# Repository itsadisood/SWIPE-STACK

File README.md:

# SWIPE-STACK

**SWIPE-STACK** is a modern re-implementation of the classic puzzle game *Tetris*, featuring a wireless glove controller and a dynamic LED-matrix-based main hub.

This project combines embedded systems design, wireless communication, real-time graphics processing, and custom hardware to create an innovative and portable gaming experience.

---

## Project Overview

The system consists of two main components:

### Glove Module
- **Input Device**: A wearable glove capturing hand movements and gestures.
- **Key Components**:
  - **IMU Sensor**: Collects motion and orientation data.
  - **STM32 Microcontroller**: Processes IMU data and converts it into game control inputs.
  - **HM19 Bluetooth Module**: Communicates inputs wirelessly to the hub via UART.
  - **LiPo Battery**: Powers the glove, with battery management provided by an off-the-shelf controller.

### Main Hub
- **Game Console**: Executes game logic, receives user input, and manages displays.
- **Key Components**:
  - **STM32 Microcontroller**: Runs the game engine and display drivers.
  - **HM19 Bluetooth Module**: Receives input data from the glove.
  - **64x32 LED Matrix Display**: Displays the active game screen, driven by a custom parallel interface using DMA and timers.
  - **OLED 16x2 Text Display**: Shows the current score and level via SPI.
  - **TI Buck Converter**: Provides regulated power for the system.

Each STM32 project (`Hub/` and `Glove/`) follows the typical CubeIDE structure, including source files (`Core/`), drivers (`Drivers/`), project configuration (`.ioc`), and build settings.

---

## Repository Structure

- **Hub/** – Firmware for the main hub (STM32 project using STM32Workbench)
- **Glove/** – Firmware for the glove controller (STM32 project using STM32Workbench)
- **Electrical/** – Hardware design files (schematics, PCB layouts)
- **Mechanical/** – Mechanical design files (CAD models for glove and hub enclosures)
- **README.md** – Project overview and documentation (this file)

---
## Features

- **Wireless Glove Controller**: Real-time gesture input using an IMU and STM32 MCU.
- **Bluetooth Communication**: Low-latency UART-based HM19 Bluetooth link.
- **Custom LED Matrix Driver**: High-speed, multiplexed driving of a 64x32 RGB LED matrix using DMA and timers.
- **Embedded Game Engine**: Fully on-board Tetris-like game running on STM32 microcontroller.
- **Text-Based Display**: OLED screen displaying real-time score and level information.
- **Portable and Modular Design**: Custom PCBs, enclosures, and battery-powered operation.

---

## Demo

Check out a live demo of SWIPE-STACK here:  

👉 [Watch the demo on YouTube](https://www.youtube.com/watch?v=645_PaOeo9Y&t=164s)

---

## Contributors

- Aditya Sood
- Alex Chitsazzadeh
- Vishnu Lagudu
- Justin Cambridge

---

## Notes

- This project is not intended for direct plug-and-play usage.
- Hardware assembly, flashing, and Bluetooth setup are required to build a fully functioning system.
- Schematics and mechanical models are provided for reference and reproduction.
- All firmware was developed using [STM32SystemWorkbench](https://www.st.com/en/development-tools/stm32cubeide.html).

---

## Acknowledgments

- STM32Cube HAL Drivers
- Public domain versions of the classic Tetris game logic
- Open-source hardware design inspirations for LED matrix driving techniques

---

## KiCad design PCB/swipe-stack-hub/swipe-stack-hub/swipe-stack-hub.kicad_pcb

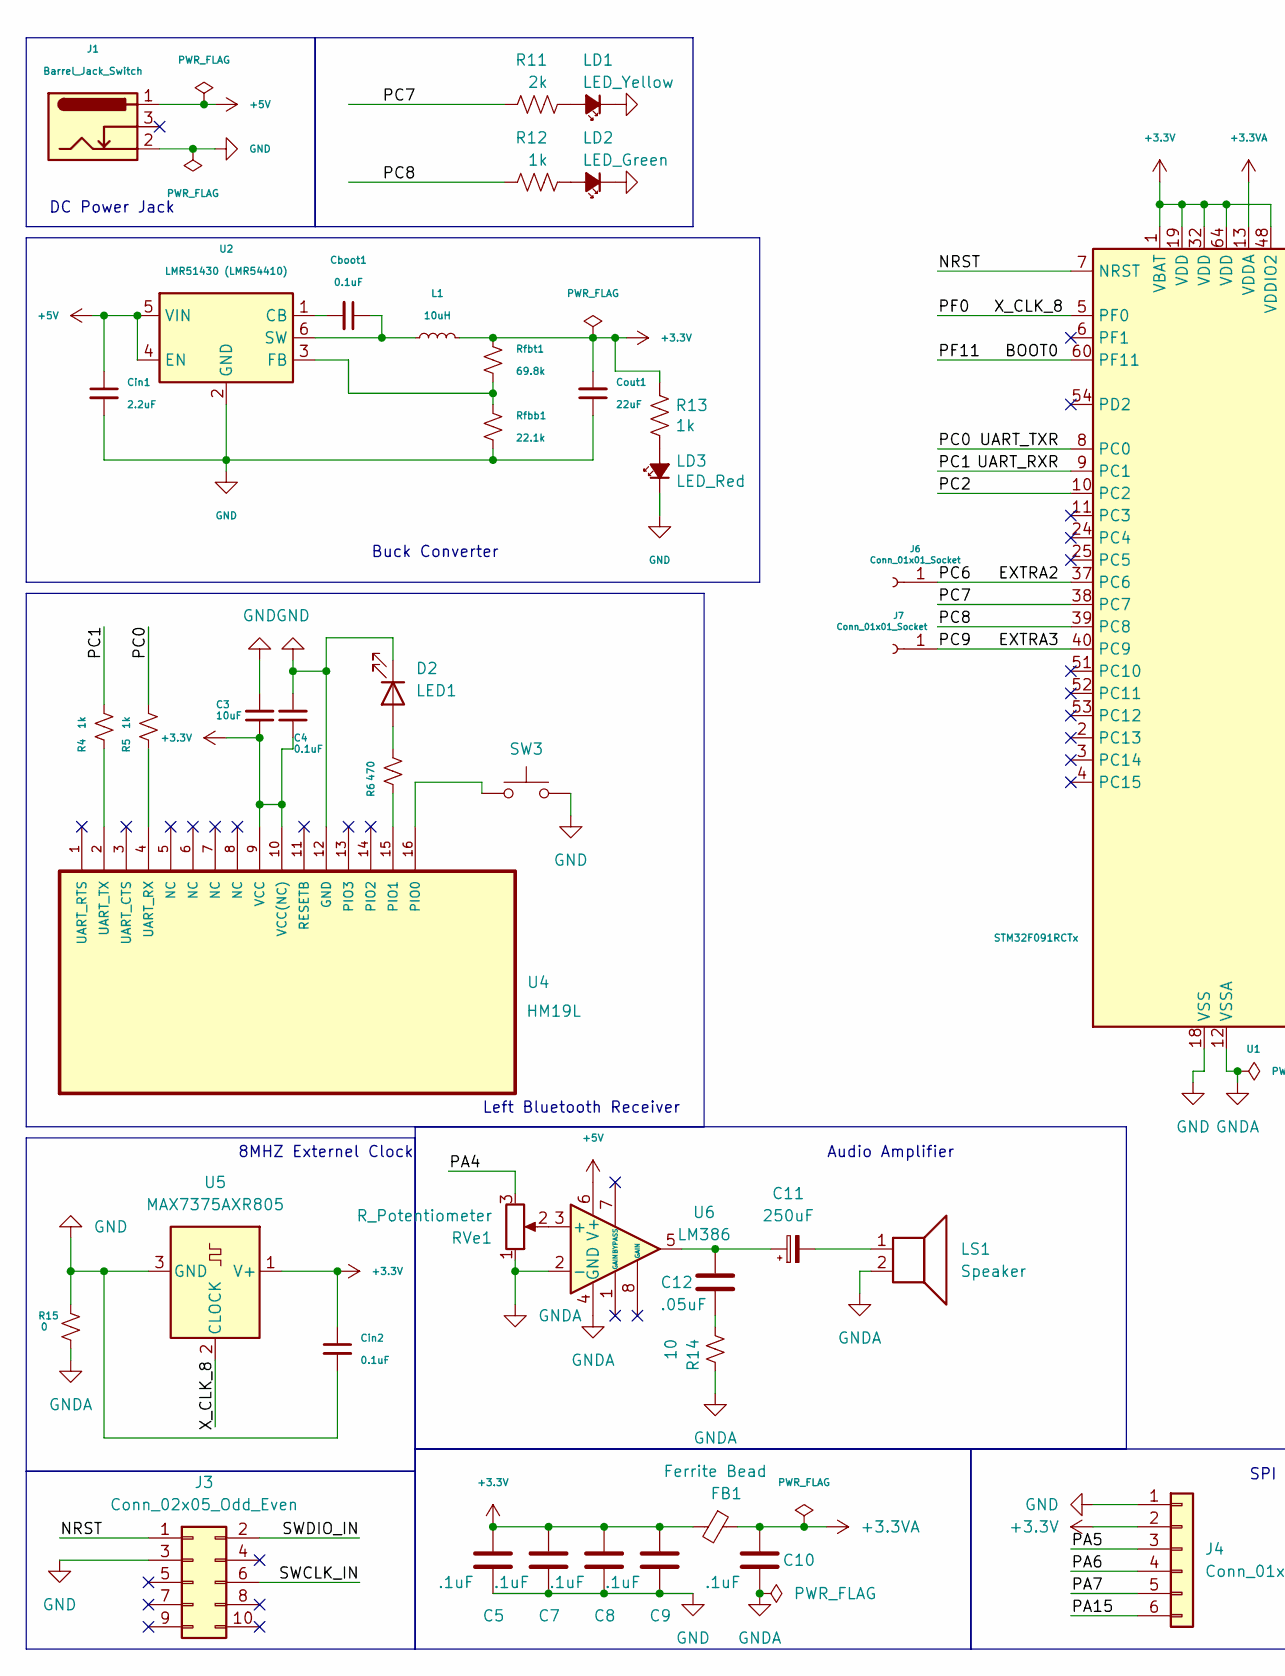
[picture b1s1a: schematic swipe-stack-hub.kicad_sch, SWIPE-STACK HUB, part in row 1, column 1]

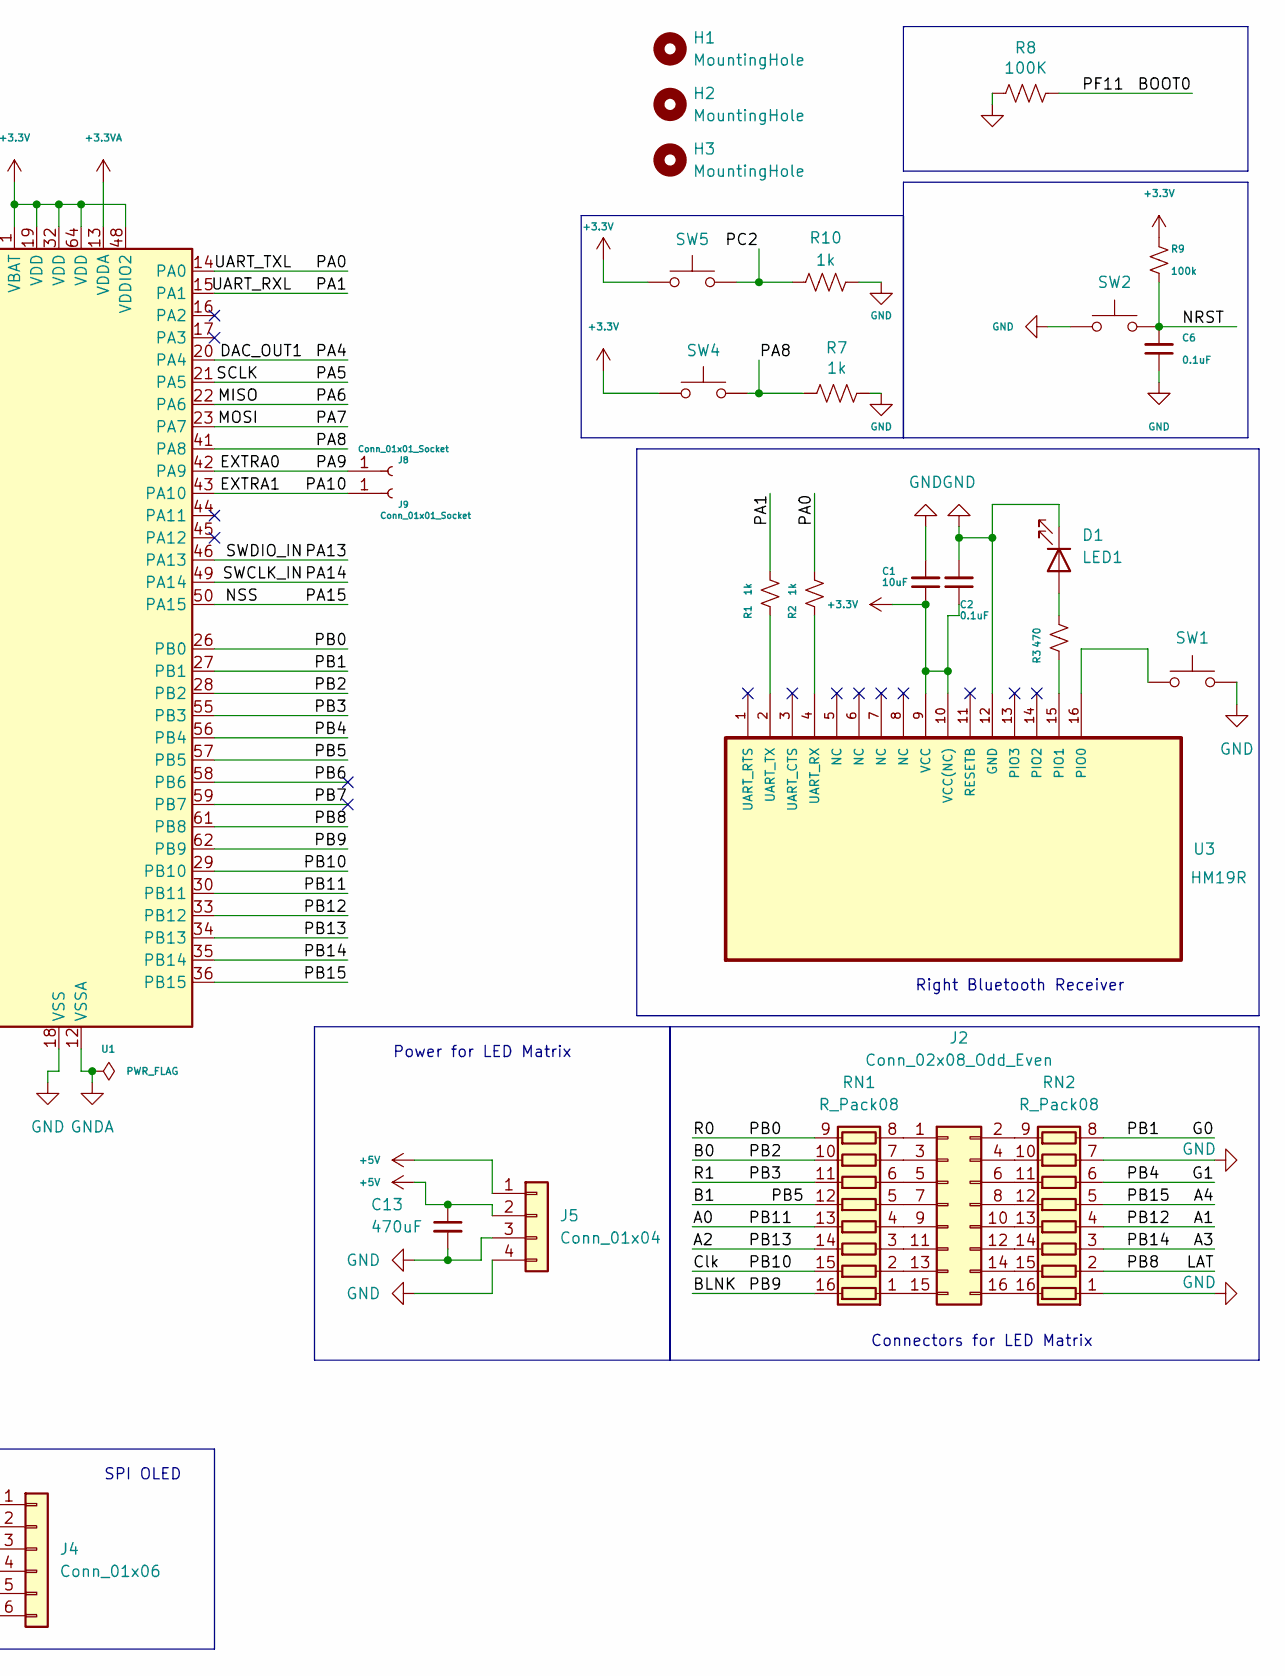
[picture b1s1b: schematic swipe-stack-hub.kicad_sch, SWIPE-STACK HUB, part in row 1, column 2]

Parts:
C1, C3: 10uF; C_0805_2012Metric_Pad1.18x1.45mm_HandSolder
C2, C4, C6: 0.1uF; C_0805_2012Metric_Pad1.18x1.45mm_HandSolder
C5, C7, C8, C9, C10: .1uF; C_0805_2012Metric_Pad1.18x1.45mm_HandSolder
C11: 250uF; CP_Radial_D14.0mm_P5.00mm
C12: .05uF; C_0805_2012Metric_Pad1.18x1.45mm_HandSolder
C13: 470uF; CP_Radial_D14.0mm_P5.00mm
Cboot1: 0.1uF; C_0805_2012Metric_Pad1.18x1.45mm_HandSolder
Cin1: 2.2uF; C_0805_2012Metric_Pad1.18x1.45mm_HandSolder
Cin2: 0.1uF; C_0805_2012Metric_Pad1.18x1.45mm_HandSolder
Cout1: 22uF; CP_Radial_D5.0mm_P2.50mm
D1, D2: LED1; LED_0805_2012Metric_Pad1.15x1.40mm_HandSolder
FB1: Ferrite Bead; L_0805_2012Metric_Pad1.15x1.40mm_HandSolder
H1, H2, H3: MountingHole; MountingHole_3mm
J1: Barrel_Jack_Switch; BarrelJack_CUI_PJ-036AH-SMT_Horizontal
J2: Conn_02x08_Odd_Even; IDC-Header_2x08_P2.54mm_Vertical_SMD
J3: Conn_02x05_Odd_Even; IDC-Header_2x05_P2.54mm_Vertical
J4: Conn_01x06; JST_VH_B6P-VH-B_1x06_P3.96mm_Vertical
J5: Conn_01x04; JST_VH_B4P-VH-B_1x04_P3.96mm_Vertical
J6, J7, J8, J9: Conn_01x01_Socket; PinSocket_1x01_P2.54mm_Vertical
L1: 10uH; L_0805_2012Metric_Pad1.15x1.40mm_HandSolder
LD1: LED_Yellow; LED_0805_2012Metric_Pad1.15x1.40mm_HandSolder
LD2: LED_Green; LED_0805_2012Metric_Pad1.15x1.40mm_HandSolder
LD3: LED_Red; LED_0805_2012Metric_Pad1.15x1.40mm_HandSolder
LS1: Speaker; JST_VH_B2P-VH-FB-B_1x02_P3.96mm_Vertical
R1, R2, R4, R5, R7, R10, R12, R13: 1k; R_0805_2012Metric_Pad1.20x1.40mm_HandSolder
R3, R6: 470; R_0805_2012Metric_Pad1.20x1.40mm_HandSolder
R8: 100K; R_0805_2012Metric_Pad1.20x1.40mm_HandSolder
R9: 100k; R_0805_2012Metric_Pad1.20x1.40mm_HandSolder
R11: 2k; R_0805_2012Metric_Pad1.20x1.40mm_HandSolder
R14: 10; R_0805_2012Metric_Pad1.20x1.40mm_HandSolder
R15: 0; R_0805_2012Metric_Pad1.20x1.40mm_HandSolder
RN1, RN2: R_Pack08; SOIC127P762X240-16N
RVe1: R_Potentiometer; Potentiometer_Bourns_PTV09A-1_Single_Vertical
Rfbb1: 22.1k; R_0805_2012Metric_Pad1.20x1.40mm_HandSolder
Rfbt1: 69.8k; R_0805_2012Metric_Pad1.20x1.40mm_HandSolder
SW1, SW2, SW3: SW_SPST_PTS645
SW4, SW5: SW_Push; SW_SPST_PTS645
U1: STM32F091RCTx; LQFP-64_10x10mm_P0.5mm
U2: LMR51430 (LMR54410); SOT-23-6
U3: HM19R; HM-19-MODULE
U4: HM19L; HM-19-MODULE
U5: MAX7375AXR805; SOT-323_SC-70_Handsoldering
U6: LM386; SOIC-8-1EP_3.9x4.9mm_P1.27mm_EP2.29x3mm

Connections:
+3.3V: C1.1, C2.1, C3.1, C4.1, C5.1, C7.1, C8.1, C9.1, Cin2.1, Cout1.2, FB1.2, J4.2, L1.2, R9.1, R13.1, Rfbt1.1, SW4.1, SW5.1, U1.1 (VBAT), U1.19 (VDD), U1.32 (VDD), U1.48 (VDDIO2), U1.64 (VDD), U3.9 (VCC), U3.10 (VCC(NC)), U4.9 (VCC), U4.10 (VCC(NC)), U5.1 (V+)
+3.3VA: C10.1, FB1.1, U1.13 (VDDA)
+5V: C13.1, Cin1.1, J1.1, J5.1, J5.2, U2.4 (EN), U2.5 (VIN), U6.6 (V+)
/A0: RN1.13 (R4.2), U1.30 (PB11)
/A1: RN2.4 (R4.1), U1.33 (PB12)
/A2: RN1.14 (R3.2), U1.34 (PB13)
/A3: RN2.3 (R3.1), U1.35 (PB14)
/A4: RN2.5 (R5.1), U1.36 (PB15)
/B0: RN1.10 (R7.2), U1.28 (PB2)
/B1: RN1.12 (R5.2), U1.57 (PB5)
/BLNK: RN1.16 (R1.2), U1.62 (PB9)
/BOOT0: R8.1, U1.60 (PF11)
/Clk: RN1.15 (R2.2), U1.29 (PB10)
/DAC_OUT1: RVe1.3, U1.20 (PA4)
/EXTRA0: J8.1, U1.42 (PA9)
/EXTRA1: J9.1, U1.43 (PA10)
/EXTRA2: J6.1, U1.37 (PC6)
/EXTRA3: J7.1, U1.40 (PC9)
/G0: RN2.8 (R8.1), U1.27 (PB1)
/G1: RN2.6 (R6.1), U1.56 (PB4)
/LAT: RN2.2 (R2.1), U1.61 (PB8)
/MISO: J4.4, U1.22 (PA6)
/MOSI: J4.5, U1.23 (PA7)
/NRST: C6.2, J3.1, R9.2, SW2.2, U1.7 (NRST)
/NSS: J4.6, U1.50 (PA15)
/PA0: R2.2, U1.14 (PA0)
/PA1: R1.2, U1.15 (PA1)
/PA5: J4.3, U1.21 (PA5)
/PA8: R7.2, SW4.2, U1.41 (PA8)
/PA13: J3.2, U1.46 (PA13)
/PA14: J3.6, U1.49 (PA14)
/PB0: RN1.9 (R8.2), U1.26 (PB0)
/PB3: RN1.11 (R6.2), U1.55 (PB3)
/PB6: U1.58 (PB6)
/PB7: U1.59 (PB7)
/PC0: R5.2, U1.8 (PC0)
/PC1: R4.2, U1.9 (PC1)
/PC2: R10.1, SW5.2, U1.10 (PC2)
/PC7: R11.2, U1.38 (PC7)
/PC8: R12.2, U1.39 (PC8)
/PF0: U1.5 (PF0), U5.2 (CLOCK)
GND: C1.2, C2.2, C3.2, C4.2, C5.2, C6.1, C7.2, C8.2, C9.2, C13.2, Cin1.2, Cin2.2, Cout1.1, D1.1 (K), D2.1 (K), J1.2, J3.3, J4.1, J5.3, J5.4, LD1.1 (K), LD2.1 (K), LD3.1 (K), R7.1, R8.2, R10.2, R15.2, RN2.1 (R1.1), RN2.7 (R7.1), Rfbb1.2, SW1.2, SW2.1, SW3.2, U1.18 (VSS), U1.31 (VSS), U1.47 (VSS), U1.63 (VSS), U2.2 (GND), U3.12 (GND), U4.12 (GND), U5.3 (GND)
GNDA: C10.2, LS1.2, R14.1, R15.1, RVe1.1, U1.12 (VSSA), U6.2 (-), U6.4 (GND)
unnamed: C11.1, C12.1, U6.5
unnamed: C11.2, LS1.1
unnamed: C12.2, R14.2
unnamed: D1.2 (A), R3.2
unnamed: D2.2 (A), R6.2
unnamed: J2.1, RN1.8 (R8.1)
unnamed: J2.2, RN2.9 (R8.2)
unnamed: J2.3, RN1.7 (R7.1)
unnamed: J2.4, RN2.10 (R7.2)
unnamed: J2.5, RN1.6 (R6.1)
unnamed: J2.6, RN2.11 (R6.2)
unnamed: J2.7, RN1.5 (R5.1)
unnamed: J2.8, RN2.12 (R5.2)
unnamed: J2.9, RN1.4 (R4.1)
unnamed: J2.10, RN2.13 (R4.2)
unnamed: J2.11, RN1.3 (R3.1)
unnamed: J2.12, RN2.14 (R3.2)
unnamed: J2.13, RN1.2 (R2.1)
unnamed: J2.14, RN2.15 (R2.2)
unnamed: J2.15, RN1.1 (R1.1)
unnamed: J2.16, RN2.16 (R1.2)
unnamed: LD1.2 (A), R11.1
unnamed: LD2.2 (A), R12.1
unnamed: LD3.2 (A), R13.2
unnamed: Cboot1.2, U2.1 (CB)
unnamed: Rfbb1.1, Rfbt1.2, U2.3 (FB)
unnamed: Cboot1.1, L1.1, U2.6 (SW)
unnamed: SW1.1, U3.16 (PIO0)
unnamed: R3.1, U3.15 (PIO1)
unnamed: R2.1, U3.4 (UART_RX)
unnamed: R1.1, U3.2 (UART_TX)
unnamed: SW3.1, U4.16 (PIO0)
unnamed: R6.1, U4.15 (PIO1)
unnamed: R5.1, U4.4 (UART_RX)
unnamed: R4.1, U4.2 (UART_TX)
unnamed: RVe1.2, U6.3 (+)

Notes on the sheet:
Right Bluetooth Receiver
Audio Amplifier
Buck Converter
SPI OLED
Power for LED Matrix
Connectors for LED Matrix
8MHZ Externel Clock
Left Bluetooth Receiver
DC Power Jack

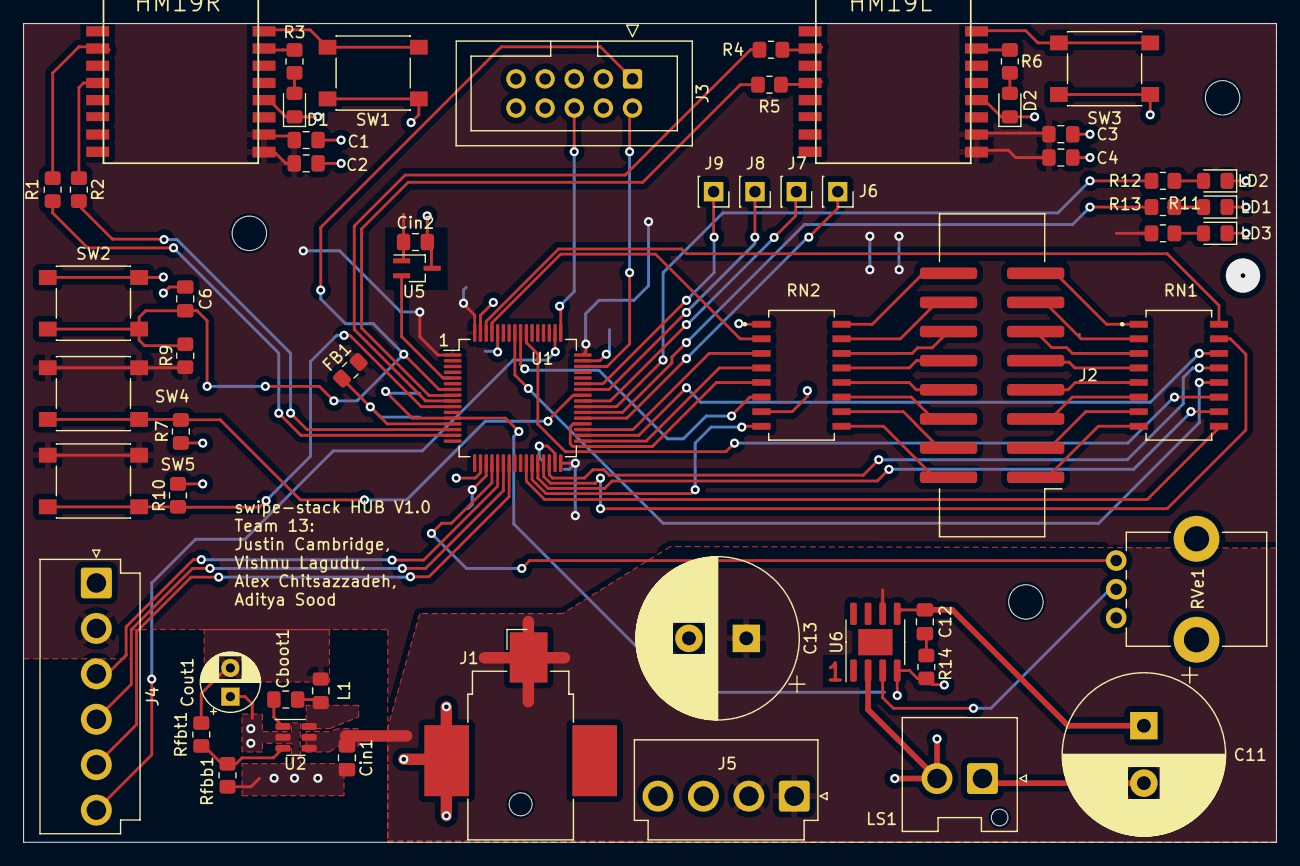
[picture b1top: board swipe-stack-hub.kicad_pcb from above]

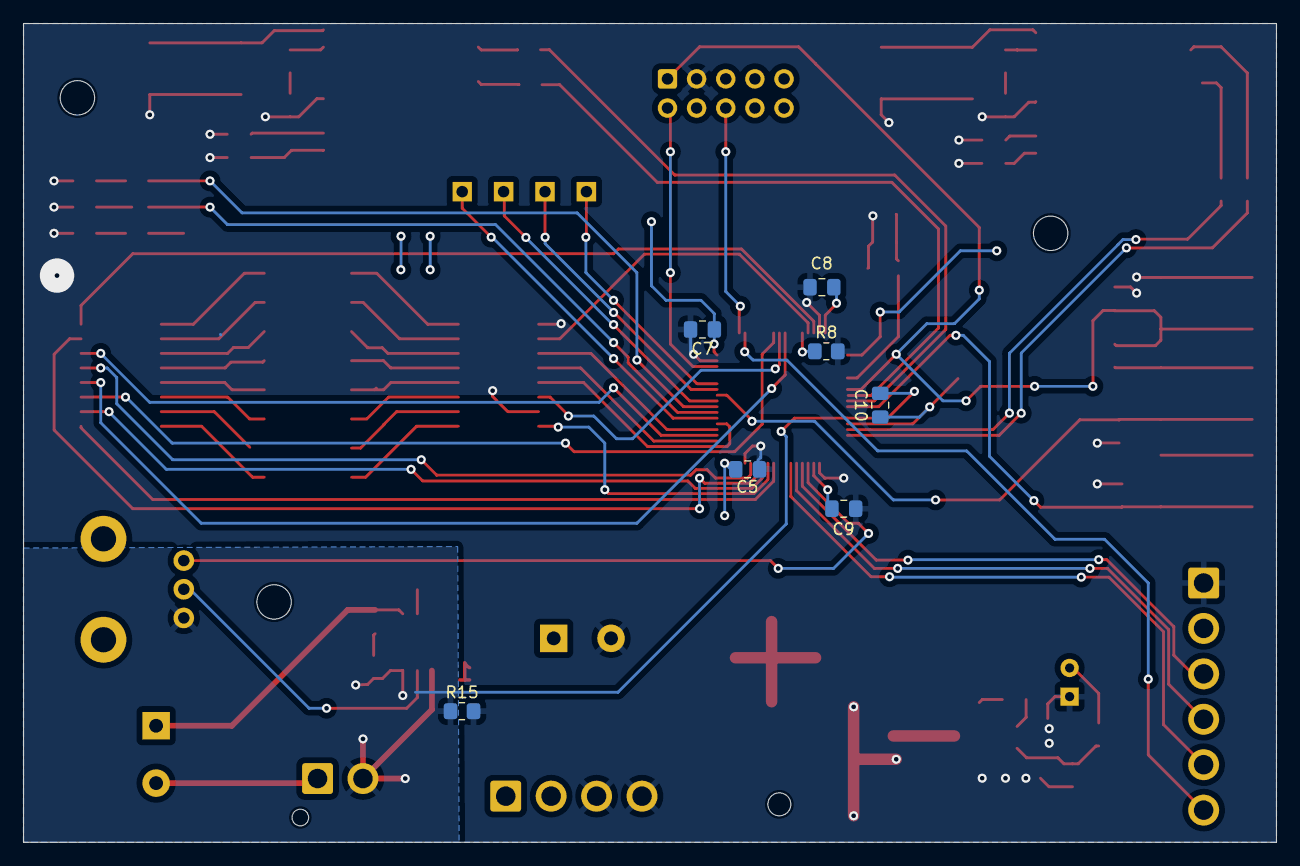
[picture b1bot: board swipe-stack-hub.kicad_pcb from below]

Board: 2 copper layers, 109.2 x 71.4 mm, 68 parts (7 on the bottom side), 77 nets.

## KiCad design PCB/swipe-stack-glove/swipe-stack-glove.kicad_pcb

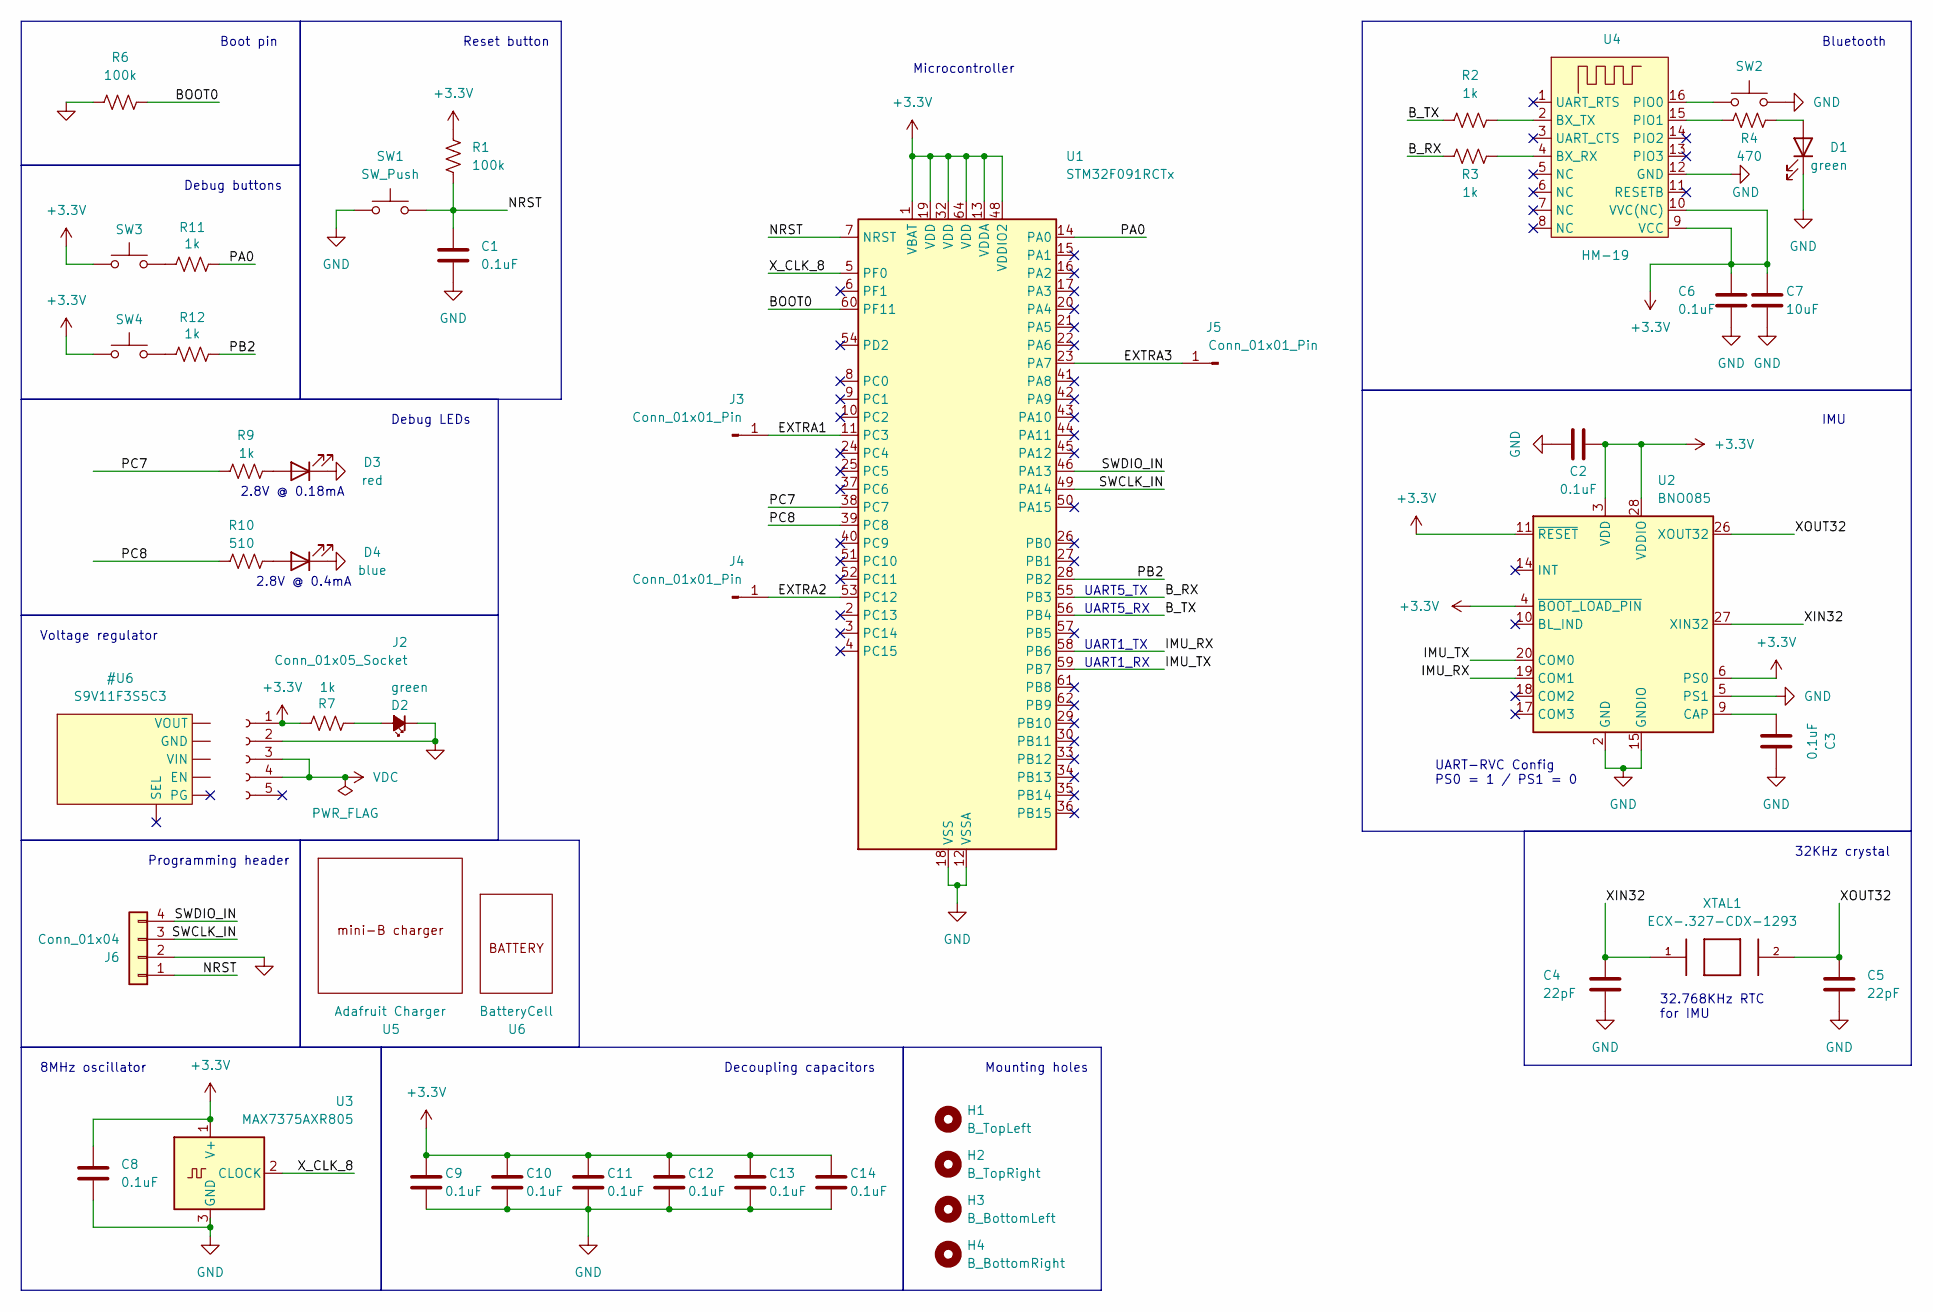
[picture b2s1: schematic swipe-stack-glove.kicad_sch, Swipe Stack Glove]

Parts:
C1, C2, C3, C6, C8, C9, C10, C11, C12, C13, C14: 0.1uF; C_0805_2012Metric_Pad1.18x1.45mm_HandSolder
C4, C5: 22pF; C_0805_2012Metric_Pad1.18x1.45mm_HandSolder
C7: 10uF; C_0805_2012Metric_Pad1.18x1.45mm_HandSolder
D1, D2: green; LED_0805_2012Metric_Pad1.15x1.40mm_HandSolder
D3: red; LED_0805_2012Metric_Pad1.15x1.40mm_HandSolder
D4: blue; LED_0805_2012Metric_Pad1.15x1.40mm_HandSolder
H1: B_TopLeft; MountingHole_2.5mm
H2: B_TopRight; MountingHole_2.5mm
H3: B_BottomLeft; MountingHole_2.5mm
H4: B_BottomRight; MountingHole_2.5mm
J2: Conn_01x05_Socket; PinHeader_1x05_P2.54mm_Vertical
J3, J4, J5: Conn_01x01_Pin; PinHeader_1x01_P2.54mm_Vertical
J6: Conn_01x04; PinHeader_1x04_P2.54mm_Vertical
R1, R6: 100k; R_0805_2012Metric_Pad1.20x1.40mm_HandSolder
R2, R3, R7: 1k; R_0805_2012Metric_Pad1.20x1.40mm_HandSolder
R4: 470; R_0805_2012Metric_Pad1.20x1.40mm_HandSolder
R9, R11, R12: 1k; LED_0805_2012Metric_Pad1.15x1.40mm_HandSolder
R10: 510; LED_0805_2012Metric_Pad1.15x1.40mm_HandSolder
SW1, SW2, SW3, SW4: SW_Push; SW_SPST_Omron_B3FS-100xP
U1: STM32F091RCTx; LQFP-64_10x10mm_P0.5mm
U2: BNO085; LGA-28_5.2x3.8mm_P0.5mm
U3: MAX7375AXR805; SOT-323_SC-70_Handsoldering
U4: HM-19; HM-11-MODULE
U5: Adafruit Charger; AdaFruit Charger
U6: BatteryCell; battery_cell
XTAL1: ECX-.327-CDX-1293; XTAL_ECS-.327-12.5-34RR-TR

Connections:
+3.3V: C2.2, C6.1, C7.1, C8.1, C9.1, C10.1, C11.1, C12.1, C13.1, C14.1, J2.1, R1.1, R7.1, SW3.1, SW4.1, U1.1 (VBAT), U1.13 (VDDA), U1.19 (VDD), U1.32 (VDD), U1.48 (VDDIO2), U1.64 (VDD), U2.3 (VDD), U2.4 (~BOOT_LOAD_PIN), U2.6 (PS0), U2.11 (~RESET), U2.28 (VDDIO), U3.1 (V+), U4.9 (VCC), U4.10 (VVC(NC))
/BOOT0: R6.2, U1.60 (PF11)
/B_RX: R3.1, U1.55 (PB3)
/B_TX: R2.1, U1.56 (PB4)
/EXTRA1: J3.1, U1.11 (PC3)
/EXTRA2: J4.1, U1.53 (PC12)
/EXTRA3: J5.1, U1.23 (PA7)
/IMU_RX: U1.58 (PB6), U2.19 (COM1)
/IMU_TX: U1.59 (PB7), U2.20 (COM0)
/NRST: C1.1, J6.1, R1.2, SW1.2, U1.7 (NRST)
/PA0: R11.1, U1.14 (PA0)
/PB2: R12.1, U1.28 (PB2)
/PC7: R9.2, U1.38 (PC7)
/PC8: R10.2, U1.39 (PC8)
/SWCLK_IN: J6.3, U1.49 (PA14)
/SWDIO_IN: J6.4, U1.46 (PA13)
/XIN32: C4.1, U2.27 (XIN32), XTAL1.1
/XOUT32: C5.1, U2.26 (XOUT32), XTAL1.2
/X_CLK_8: U1.5 (PF0), U3.2 (CLOCK)
GND: C1.2, C2.1, C3.2, C4.2, C5.2, C6.2, C7.2, C8.2, C9.2, C10.2, C11.2, C12.2, C13.2, C14.2, D1.1 (K), D2.1 (K), D3.1 (K), D4.1 (K), J2.2, J6.2, R6.1, SW1.1, SW2.2, U1.12 (VSSA), U1.18 (VSS), U1.31 (VSS), U1.47 (VSS), U1.63 (VSS), U2.2 (GND), U2.5 (PS1), U2.15 (GNDIO), U2.16 (GNDIO), U2.25 (GNDIO), U3.3 (GND), U4.12 (GND)
unnamed: D1.2 (A), R4.2
unnamed: D2.2 (A), R7.2
unnamed: D3.2 (A), R9.1
unnamed: D4.2 (A), R10.1
unnamed: R11.2, SW3.2
unnamed: R12.2, SW4.2
unnamed: C3.1, U2.9 (CAP)
unnamed: R3.2, U4.4 (BX_RX)
unnamed: R2.2, U4.2 (BX_TX)
unnamed: SW2.1, U4.16 (PIO0)
unnamed: R4.1, U4.15 (PIO1)
VDC: J2.3, J2.4

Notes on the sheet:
Boot pin
UART5_RX
Decoupling capacitors
UART1_RX
Reset button
32.768KHz RTC for IMU
Bluetooth
Debug buttons
Voltage regulator
8MHz oscillator
2.8V @ 0.18mA
32KHz crystal
UART1_TX
Mounting holes
UART5_TX
Programming header
2.8V @ 0.4mA
Microcontroller
UART-RVC Config PS0 = 1 / PS1 = 0
Debug LEDs
IMU

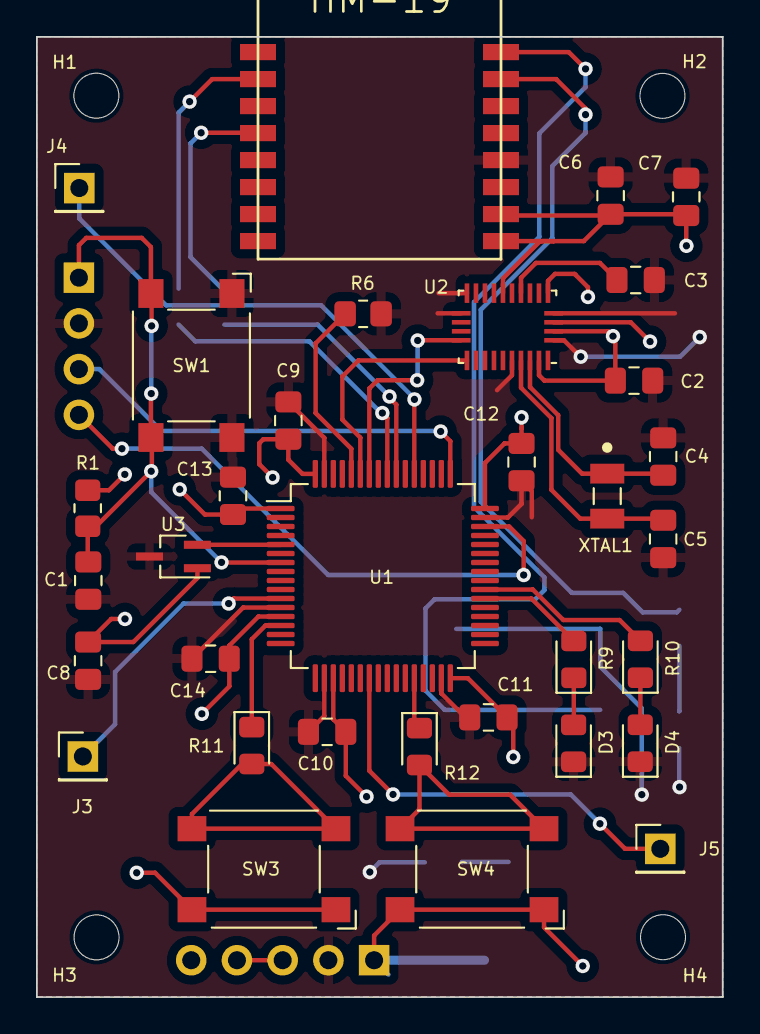
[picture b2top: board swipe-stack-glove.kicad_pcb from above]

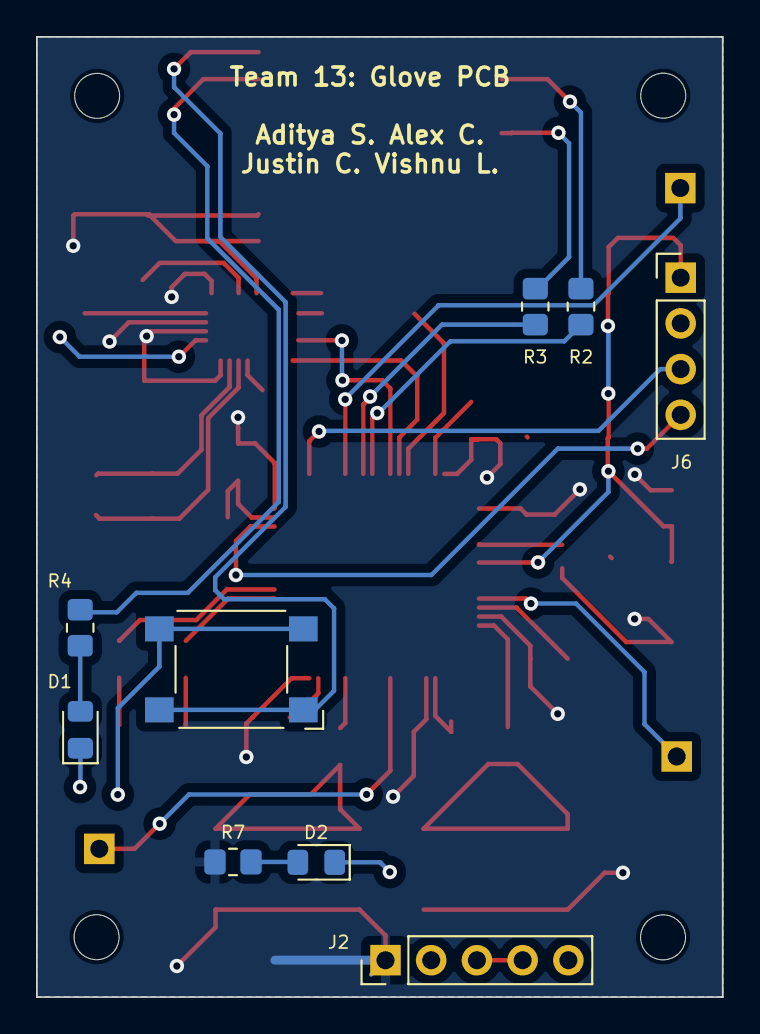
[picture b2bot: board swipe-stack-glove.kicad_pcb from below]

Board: 2 copper layers, 38.1 x 53.3 mm, 46 parts (9 on the bottom side), 32 nets.

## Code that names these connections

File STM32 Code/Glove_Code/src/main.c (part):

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
/** Pin definitions:

  PB3 -> UART5_TX -> B_RX
 B_TX -> UART5_RX -> PB4

    PB5 -> UART1_TX -> IMU_RX (not used)
 IMU_TX -> UART1_RX -> PB6

**/

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void setup_BX_GPIO()
{
	RCC -> AHBENR |= RCC_AHBENR_GPIOBEN;                    // Enable GPIO clock
	GPIOB -> MODER |= GPIO_MODER_MODER3_1; 					// PB3 is TX to Bluetooth (Alt Mode)
	GPIOB -> AFR[0] |= 0x4 << 12;							// PB3 selected for USART5_TX
	GPIOB -> MODER |= GPIO_MODER_MODER4_1; 					// PB4 is RX from Bluetooth (Alt Mode)
	GPIOB -> AFR[0] |= 0x4 << 16; 							// PB4 selected for USART5_RX
}

void setup_BX_UART()
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void setup_IMU_GPIO(void)
{
	RCC->AHBENR |= RCC_AHBENR_GPIOBEN;					// portB clock
	GPIOB->MODER &= ~(GPIO_MODER_MODER7);				// clearing PB7 to input
	GPIOB->MODER |= GPIO_MODER_MODER7_1; 				// setting PB7 to AFR mode (UART)
	GPIOB->AFR[0] &= ~(GPIO_AFRL_AFRL7); 	   			// selecting AF0 for PB7

	RCC->APB2ENR |= RCC_APB2ENR_SYSCFGCOMPEN;  			// enable syscfg clock
	SYSCFG->EXTICR[0] &= SYSCFG_EXTICR1_EXTI0_PA; 		// enable pa0 on EXTI0
	RCC->AHBENR |= RCC_AHBENR_GPIOAEN;					// portA clock
	GPIOA->MODER &= ~(GPIO_MODER_MODER0);				// clearing PA0 to
	EXTI->RTSR |= EXTI_RTSR_TR0;						// interrupt on Rising edge PA0
	EXTI->IMR |= EXTI_IMR_MR0;							// enable PA0 interrupt
	NVIC->ISER[0] |= (1 << EXTI0_1_IRQn);
}

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
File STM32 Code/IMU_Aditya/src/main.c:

/**
  ******************************************************************************
  * @file    main.c
  * @author  Ac6
  * @version V1.0
  * @date    01-December-2013
  * @brief   Default main function.
  ******************************************************************************
*/

#include "stm32f0xx.h"
#include "BNO08x.h" // library for IMU functions
#include <stdint.h>

uint8_t tx_cargo[300];
uint8_t rx_cargo[300];

//**********************************************
// function to configure GPIO as needed
// PB12 => SPI2_NSS [manually driven]
// PB13 => SPI2_SCK
// PB14 => SPI2_MOSI
// PB15 => SPI2_MISO
// PB8 => INT (input to micro)
// PB10 => RST (output from micro)
//
void setup_GPIO(void)
{
	RCC -> AHBENR |= RCC_AHBENR_GPIOBEN;
	GPIOB -> MODER &= ~ (GPIO_MODER_MODER8 & GPIO_MODER_MODER10 & GPIO_MODER_MODER12 & GPIO_MODER_MODER13 & GPIO_MODER_MODER14 & GPIO_MODER_MODER15);
	GPIOB -> MODER |= GPIO_MODER_MODER12_0 | GPIO_MODER_MODER13_1 | GPIO_MODER_MODER14_1 | GPIO_MODER_MODER15_1 | GPIO_MODER_MODER10_0;
	GPIOB -> AFR[1] &= ~ (GPIO_AFRH_AFR13 & GPIO_AFRH_AFR14 & GPIO_AFRH_AFR15);

	// Perform IMU cleaning
	toggle_RST(1);
	nano_wait(10000000); //10ms
	toggle_RST(0);
	toggle_NSS(0);
}


void setup_SPI(void)
{
	RCC -> APB1ENR |= RCC_APB1ENR_SPI2EN;       // enable spi2 clock
	SPI2 -> CR1 &= ~SPI_CR1_SPE;                // clear enable bit (to update config)
	SPI2 -> CR1 |= SPI_CR1_MSTR;                // master mode
	SPI2 -> CR1 |= (SPI_CR1_BR_0 | SPI_CR1_BR_1 | SPI_CR1_BR_2); // lowest baud rate (48Mhz / 256)
	SPI2 -> CR2 = SPI_CR2_DS_0 | SPI_CR2_DS_1 | SPI_CR2_DS_2;    // 8 bit size of data
	SPI2 -> CR2 |= SPI_CR2_SSOE | SPI_CR2_NSSP; // output enable and nssp enable
	SPI2 -> CR2 |= SPI_CR2_TXDMAEN | SPI_CR2_RXDMAEN;
	SPI2 -> CR1 |= SPI_CR1_SPE;
}

void init_exti(void)
{
	RCC -> APB2ENR |= RCC_APB2ENR_SYSCFGCOMPEN;
	SYSCFG -> EXTICR[2] |=  SYSCFG_EXTICR3_EXTI8_PB;
	EXTI -> IMR |= EXTI_IMR_MR8;
	EXTI -> FTSR |= EXTI_FTSR_TR8;
	NVIC -> ISER[0] |= (1 << EXTI4_15_IRQn);
}

void EXTI4_15_IRQHandler(void) {
    EXTI -> PR |= EXTI_PR_PR8;
    get_startup_adv(tx_cargo, rx_cargo);
}

int main(void)
{
	memset(tx_cargo, 0, 300);
	memset(rx_cargo, 0, 300);
	setup_GPIO();
	setup_SPI();
	init_exti();

	while(1)
	{
		asm("wfi");
	}
}

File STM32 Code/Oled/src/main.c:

/**
  ******************************************************************************
  * @file    main.c
  * @author  Ac6
  * @version V1.0
  * @date    01-December-2013
  * @brief   Default main function.
  ******************************************************************************
*/


#include "stm32f0xx.h"
#include <stdio.h>

uint16_t score[34] = {
				0x002, // Command to set the cursor at the first position line 1
		        0x200+'S', 0x200+'C', 0x200+'O', 0x200+'R', 0x200+'E', + 0x200+':', 0x200+' ', 0x200+' ',
		        0x200+' ', 0x200+' ', 0x200+' ', 0x200+' ', + 0x200+' ', 0x200+' ', 0x200+' ', 0x200+' ',
		        0x0c0, // Command to set the cursor at the first position line 2
		        0x200+'0', 0x200+'0', 0x200+'0', 0x200+'0', 0x200+'0', + 0x200+'0', 0x200+'0', 0x200+'0',
		        0x200+'0', 0x200+'0', 0x200+'0', 0x200+'0', + 0x200+'0', 0x200+'0', 0x200+'0', 0x200+'0',
};

char scoreBuff[17] = {0x0, 0x0, 0x0, 0x0, 0x0, 0x0, 0x0, 0x0, 0x0, 0x0, 0x0, 0x0, 0x0, 0x0, 0x0, 0x0, 0x0};

void nano_wait(unsigned int n) {
    asm(    "        mov r0,%0\n"
            "repeat: sub r0,#83\n"
            "        bgt repeat\n" : : "r"(n) : "r0", "cc");
}

void updt_score(int digitLen)
{
	int scoreIndex = 33;
	while(digitLen != 0)
	{
		score[scoreIndex] = 0x200 + scoreBuff[(digitLen - 1)];
		digitLen--;
		scoreIndex--;
	}
}

int main(void)
{
	uint64_t scoreNum = 0;
	setupGPIO_spi();
    init_spi1();
    spi1_init_display();
    spi1_setup_dma();
    scoreNum = 0;
    int len;

    for(;;)
    {
    	nano_wait(100000000);
    	scoreNum += 23;
    	sprintf(scoreBuff, "%llu", scoreNum);
    	len = strlen(scoreBuff);
    	updt_score(len);
    }
}




void setupGPIO_spi(){
	// PA5  SPI1_SCK
	// PA6  SPI1_MISO
	// PA7  SPI1_MOSI
	// PA15 SPI1_NSS

	// GPIOA config
	RCC -> AHBENR |= RCC_AHBENR_GPIOAEN;
	GPIOA -> MODER &= ~(GPIO_MODER_MODER5  | GPIO_MODER_MODER6 | GPIO_MODER_MODER7 | GPIO_MODER_MODER15);
	GPIOA -> MODER |= (GPIO_MODER_MODER5_1 | GPIO_MODER_MODER6_1 | GPIO_MODER_MODER7_1 | GPIO_MODER_MODER15_1);
	// ports correspond to AF0 according to table
	GPIOA -> AFR[0] &= ~(0xf << (4 * 5));        // clr AFR5 -> using AF0
	GPIOA -> AFR[0] &= ~(0xf << (4 * 6));        // clr AFR6 -> using AF0
	GPIOA -> AFR[0] &= ~(0xf << (4 * 7));        // clr AFR7 -> using AF0
	GPIOA -> AFR[1] &= ~(0xf << (4 * (15 - 8))); // clr AFR15 -> using AF0
}

void init_spi1(){
	// PA5  SPI1_SCK
	// PA6  SPI1_MISO
	// PA7  SPI1_MOSI
	// PA15 SPI1_NSS

	// SPI1 config
	RCC -> APB2ENR |= RCC_APB2ENR_SPI1EN;
	SPI1 -> CR1 &= ~SPI_CR1_SPE; // disable SPI channel
	SPI1 -> CR1 |= SPI_CR1_BR; // BR = 111 -> fclk / 256
	SPI1 -> CR2 = SPI_CR2_DS_0 | SPI_CR2_DS_3; // 10 bit word size
	SPI1 -> CR1 |= SPI_CR1_MSTR; // set spi channel to MASTER mode
	SPI1 -> CR2 |= SPI_CR2_SSOE; // set slave select output enable bit
	SPI1 -> CR2 |= SPI_CR2_NSSP; // automatically pulse NSS between data transfers
	SPI1 -> CR2 |= SPI_CR2_TXDMAEN; // when transmit buffer empty, trigger DMA
	SPI1 -> CR1 |= SPI_CR1_SPE; // enable SPI channel
}

void spi1_setup_dma(void)
{
    // Note: SPI1_TX works with DMA Channel 3
    // enable clock for DMA
    RCC -> AHBENR |= RCC_AHBENR_DMAEN;
    DMA1_Channel3 -> CCR &= ~DMA_CCR_EN; // turn off DMAch3
    // set CPAR to SPI1 -> DR address
    DMA1_Channel3 -> CPAR = (uint32_t) &(SPI1 -> DR);
    // set CMA to display array base address
    DMA1_Channel3 -> CMAR = (uint32_t) score;
    // set to transfer 34 'elements' total
    DMA1_Channel3 -> CNDTR = 34;
    // set DIR for mem -> peripheral
    DMA1_Channel3 -> CCR |= DMA_CCR_DIR; // read from mem
    // set MINC to increment CMAR upon each transfer
    DMA1_Channel3 -> CCR |= DMA_CCR_MINC;
    // set memory data size to 16-bit and peripheral size to 16 bit
    DMA1_Channel3 -> CCR &= ~DMA_CCR_MSIZE; // clr msize
    DMA1_Channel3 -> CCR &= ~DMA_CCR_PSIZE; // clr psize
    DMA1_Channel3 -> CCR |= 0x00000500; // set p and m to 16 bits
    // set to circular operation
    DMA1_Channel3 -> CCR |= DMA_CCR_CIRC;

    DMA1_Channel3 -> CCR |= DMA_CCR_EN; // turn on DMAch3
}

void spi_cmd(unsigned int data)
{
    while(!(SPI1->SR & SPI_SR_TXE)) {}
    SPI1->DR = data;
}

void spi1_init_display()
{
    nano_wait(1000000); // wait 1 ms
    spi_cmd(0x38); // set for 8-bit operation
    spi_cmd(0x08); // turn display off
    spi_cmd(0x01); // clear display
    nano_wait(2000000); // wait 2 ms
    spi_cmd(0x06); // set display to scroll
    spi_cmd(0x02); // move cursor to home position
    spi_cmd(0x0c); // turn display on
}

void spi1_display1(const char *string)
{
    spi_cmd(0x02); // move cursor to home position
    while(*string != '\0')
    {
        spi_cmd(*string | 0x200); // write char to DDRAM
        string++;
    }
}

void spi1_display2(const char *string)
{
	spi_cmd(0xc0); // move cursor to lower row (offset 0x40)
    while(*string != '\0')
    {
        spi_cmd(*string | 0x200); // write char to DDRAM
        string++;
    }
}

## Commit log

2024-01-18 Added a gitignore
2024-01-18 Partition docs
2024-01-18 modify
2024-01-18 Bx Init
2024-01-19 bx working
2024-01-19 Add more methods
2024-01-20 tetris in python
2024-01-24 RDR register on uart finally working + updated exit success conditions on returns from functions
2024-01-24 Added some small things
2024-01-24 random change
2024-01-24 Modified game
2024-01-26 Prototype Code for STM32F0 Finished for Now
2024-01-27 ui works
2024-01-30 Idk what this is
2024-01-31 Using USART5 rather than USART4
2024-01-31 added .gitignore
2024-01-31 Init IMU Code (aditya)
2024-01-31 more change
2024-02-01 Add HUB75
2024-02-01 Sending data over DMA / SPI
2024-02-01 Clean communication with IMU
2024-02-01 trying to read the advertisement
2024-02-02 Create font and driver
2024-02-02 Deadly code
2024-02-04 New UART_RVC based IMU working
2024-02-04 New uart-rvc working
2024-02-05 Updated swipe-stack hub schematic with HM19 modules as well as reset button circuitry for MCU
2024-02-06 Create test
2024-02-06 UART code for iMU
2024-02-13 Get fill_disp() working
2024-02-15 matrix with DMA
2024-02-15 working (kind of)
2024-02-16 bb works
2024-02-17 playing with the timers
2024-02-17 MATRIX GO BRRRRRRRRR
2024-02-19 First cut of hub PCB
2024-02-20 Justin's version of hub PCB
2024-02-21 Glove PCB rev1
2024-02-21 changed some capacitors
2024-02-21 now with 64 colors
2024-02-22 PWM working with packed structs and wavetable go brrrrr
2024-02-28 pcb changes
2024-02-28 uhhhhhh
2024-02-29 Latest glove pcb
2024-02-29 Merged all latest PCBs
2024-03-01 pcb ready for presentation
2024-03-01 My changes
2024-03-03 Roll detection works, cleanup previous IMU code
2024-03-08 gerber done
2024-03-21 Latest STM32 code. Still need to fix some things by putting them in git ignore
2024-03-21 Added the correct hub75
2024-03-22 Fixed the matrix pinout
2024-03-25 added fall timer and button interrupts
2024-03-26 Modifications to vars and suggestions
2024-03-26 Fixed rotation and bounds check
2024-03-27 Get right left and rotation working
2024-03-27 Row clear on game side
2024-03-27 Dummy commit that im going to merge over
2024-03-28 Row clear working and added basic lose condition
2024-03-28 Gotta fix the heisenbug
2024-03-29 Fix Heisenbug, add lose condition, queue
2024-03-30 Finish game logic
2024-04-01 Working on glove soft
2024-04-03 optimize some logic
2024-04-03 Fix indent
2024-04-03 Fix indentation
2024-04-03 optimizw code and make clear constants
2024-04-03 IMU code without debouncing motion
2024-04-04 Debounce implemented, working great
2024-04-05 add bluetooth driver
2024-04-05 deprecated old IMU code
2024-04-05 modify glove code
2024-04-06 Fixed ?
2024-04-06 commited new tuned glove_code
2024-04-06 fixed
2024-04-06 fixed unmerged file
2024-04-06 finish the pheriphals for bt
2024-04-06 Updated glove bt functions a bit
2024-04-06 bt driver
2024-04-07 SWIPESTACK V1.0 (technically works, but input queue needed to boost speed and glove needs tuning too
2024-04-08 Integrated OLED drivers, scoring system, and leveling system to game logic
2024-04-09 fixed level up logic
2024-04-09 added OLED stuff again
2024-04-10 fixed level speed and typeface
2024-04-10 Latest glove code
2024-04-11 Implemented fonts, splash screen, game over screen, and all that extra stuff.
2024-04-11 Updated splash screen to scroll continuously, blocks fall faster, and centered text better
2024-04-23 Made level threshold more generous and uncapped level
2024-05-03 Final glove code
